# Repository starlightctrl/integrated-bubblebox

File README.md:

### TO-DO

Write read-me

#Integrated PCB for UMS Ultra's Bubblebox, based on Quark's Open Rectangle Template

 WIP

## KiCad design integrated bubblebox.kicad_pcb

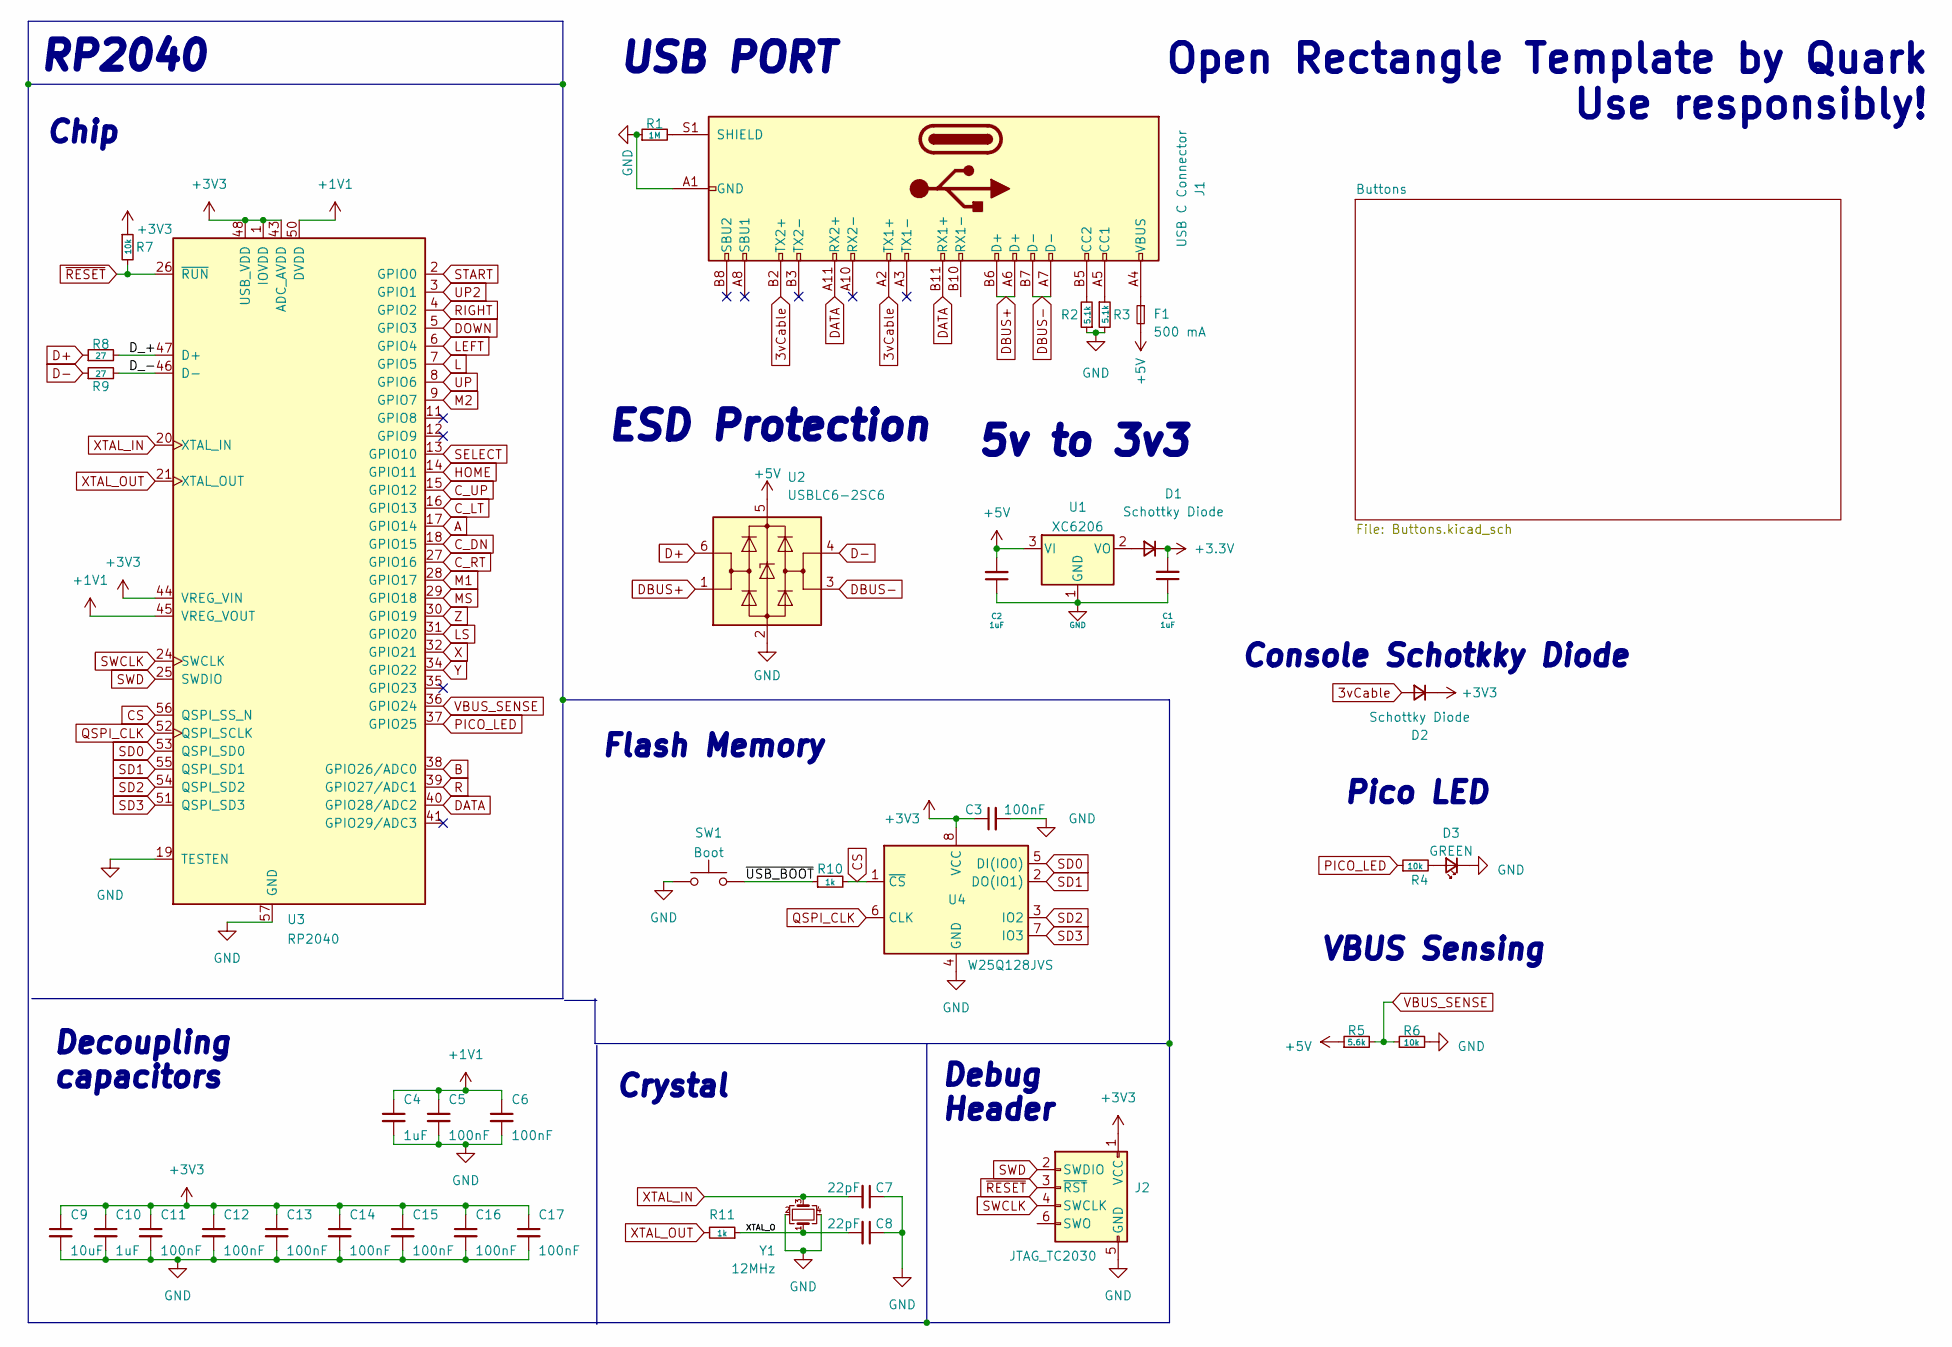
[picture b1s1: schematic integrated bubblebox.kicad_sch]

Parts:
C1, C2, C4, C10: 1uF; C_0402_1005Metric; LCSC C52923
C3, C5, C6, C11, C12, C13, C14, C15, C16, C17: 100nF; C_0402_1005Metric; LCSC C1525
C7, C8: 22pF; C_0402_1005Metric; LCSC C1555
C9: 10uF; C_0402_1005Metric; LCSC C15525
D1, D2: Schottky Diode; D_SOD-123; LCSC C8598
D3: GREEN; LED_0805_2012Metric; LCSC C2297
F1: 500 mA; Fuse_1206_3216Metric; LCSC C70076
J1: USB C Connector; TYPE-C_24P_QCHT; LCSC C456013
J2: JTAG_TC2030; Tag-Connect_TC2030-IDC-NL_2x03_P1.27mm_Vertical
R1: 1M; R_0603_1608Metric; LCSC C22935
R2, R3: 5.1k; R_0402_1005Metric; LCSC C25905
R4, R7: 10k; R_0402_1005Metric; LCSC C25744
R5: 5.6k; R_0603_1608Metric; LCSC C23189
R6: 10k; R_0603_1608Metric; LCSC C25804
R8, R9: 27; R_0603_1608Metric; LCSC C25190
R10, R11: 1k; R_0402_1005Metric; LCSC C11702
SW1: Boot; SW_SPST_SKQG_WithStem; LCSC C318884
U1: XC6206; SOT-23; LCSC C5446
U2: USBLC6-2SC6; SOT-23-6; LCSC C7519
U3: RP2040; RP2040-QFN-56; LCSC C2040
U4: W25Q128JVS; SOIC-8_5.23x5.23mm_P1.27mm; LCSC C97521
Y1: 12MHz; Crystal_SMD_3225-4Pin_3.2x2.5mm; LCSC C9002

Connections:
3vCable: D2.2 (A), J1.A2 (TX1+), J1.B2 (TX2+)
+1V1: C4.1, C5.1, C6.1, U3.23 (DVDD), U3.45 (VREG_VOUT), U3.50 (DVDD)
+5V: C2.2, F1.2, R5.1, U1.3 (VI), U2.5 (VBUS)
/D_+: R8.2, U3.47 (D+)
/D_-: R9.2, U3.46 (D-)
/XTAL_O: C8.2, R11.1, Y1.1
/~USB_BOOT: R10.1, SW1.2
A: U3.17 (GPIO14); also elsewhere on the board
B: U3.38 (GPIO26/ADC0); also elsewhere on the board
CS: R10.2, U3.56 (QSPI_SS_N), U4.1 (~CS)
C_DN: U3.18 (GPIO15); also elsewhere on the board
C_LT: U3.16 (GPIO13); also elsewhere on the board
C_RT: U3.27 (GPIO16); also elsewhere on the board
C_UP: U3.15 (GPIO12); also elsewhere on the board
D+: R8.1, U2.6 (I/O1)
D-: R9.1, U2.4 (I/O2)
DATA: J1.A11 (RX2+), J1.B11 (RX1+), U3.40 (GPIO28/ADC2)
DBUS+: J1.A6 (D+), J1.B6 (D+), U2.1 (I/O1)
DBUS-: J1.A7 (D-), J1.B7 (D-), U2.3 (I/O2)
GND: C1.1, C2.1, C3.2, C4.2, C5.2, C6.2, C7.1, C8.1, C9.2, C10.2, C11.2, C12.2, C13.2, C14.2, C15.2, C16.2, C17.2, D3.1 (K), J1.A1 (GND), J1.A12 (GND), J1.B1 (GND), J1.B12 (GND), J2.5 (GND), R1.1, R2.1, R3.2, R6.2, SW1.1, U1.1 (GND), U2.2 (GND), U3.19 (TESTEN), U3.57 (GND), U4.4 (GND), Y1.2, Y1.4; also elsewhere on the board
HOME: U3.14 (GPIO11); also elsewhere on the board
L: U3.7 (GPIO5); also elsewhere on the board
LEFT: U3.6 (GPIO4); also elsewhere on the board
LS: U3.31 (GPIO20); also elsewhere on the board
M1: U3.28 (GPIO17); also elsewhere on the board
M2: U3.9 (GPIO7); also elsewhere on the board
MS: U3.29 (GPIO18); also elsewhere on the board
unnamed: D1.2 (A), U1.2 (VO)
unnamed: D3.2 (A), R4.2
unnamed: F1.1, J1.A4 (VBUS), J1.A9 (VBUS), J1.B4 (VBUS), J1.B9 (VBUS)
unnamed: J1.A5 (CC1), R3.1
unnamed: J1.B5 (CC2), R2.2
unnamed: J1.S1 (SHIELD), R1.2
PICO_LED: R4.1, U3.37 (GPIO25)
QSPI_CLK: U3.52 (QSPI_SCLK), U4.6 (CLK)
R: U3.39 (GPIO27/ADC1); also elsewhere on the board
SD0: U3.53 (QSPI_SD0), U4.5 (DI(IO0))
SD1: U3.55 (QSPI_SD1), U4.2 (DO(IO1))
SD2: U3.54 (QSPI_SD2), U4.3 (IO2)
SD3: U3.51 (QSPI_SD3), U4.7 (IO3)
SELECT: U3.13 (GPIO10); also elsewhere on the board
START: U3.2 (GPIO0); also elsewhere on the board
SWCLK: J2.4 (SWCLK), U3.24 (SWCLK)
SWD: J2.2 (SWDIO), U3.25 (SWDIO)
UP: U3.8 (GPIO6); also elsewhere on the board
UP2: U3.3 (GPIO1); also elsewhere on the board
VBUS_SENSE: R5.2, R6.1, U3.36 (GPIO24)
X: U3.32 (GPIO21); also elsewhere on the board
XTAL_IN: C7.2, U3.20 (XTAL_IN), Y1.3
XTAL_OUT: R11.2, U3.21 (XTAL_OUT)
Y: U3.34 (GPIO22); also elsewhere on the board
Z: U3.30 (GPIO19); also elsewhere on the board
~RESET: J2.3 (~RST), R7.2, U3.26 (~RUN)

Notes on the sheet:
Console Schotkky Diode
Crystal
USB PORT
Flash Memory
Pico LED
Open Rectangle Template by Quark Use responsibly!
RP2040
Debug Header
VBUS Sensing
Chip
5v to 3v3
ESD Protection
Decoupling capacitors

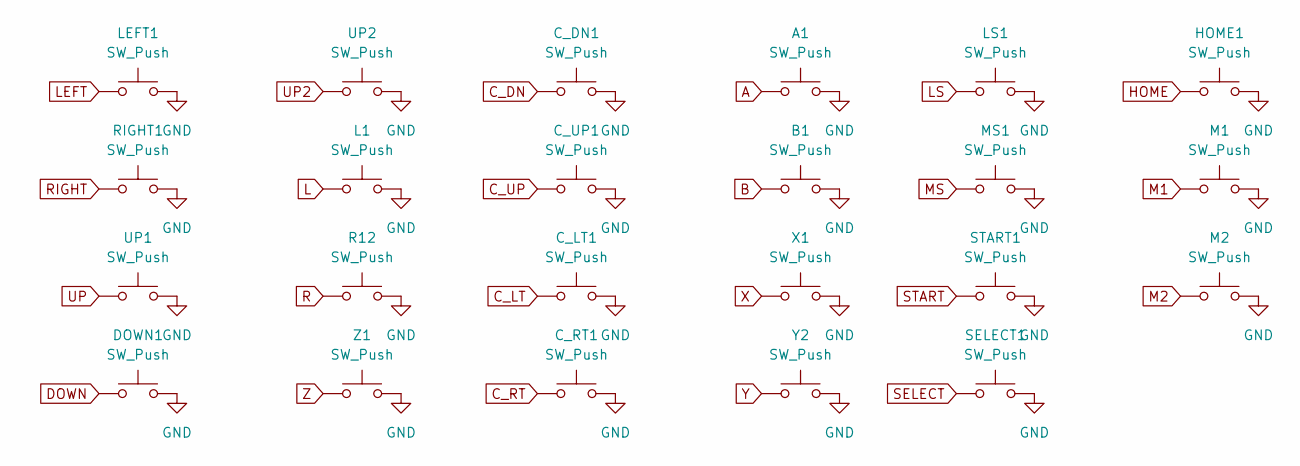
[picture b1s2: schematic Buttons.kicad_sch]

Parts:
A1: SW_Push; Kailh_socket_MX_optional
B1: SW_Push; Kailh_socket_MX_optional
C_DN1: SW_Push; Kailh_socket_MX_optional
C_LT1: SW_Push; Kailh_socket_MX_optional
C_RT1: SW_Push; Kailh_socket_MX_optional
C_UP1: SW_Push; Kailh_socket_MX_optional
DOWN1: SW_Push; Kailh_socket_MX_optional
HOME1: SW_Push; Kailh_socket_MX_optional
L1: SW_Push; Kailh_socket_MX_optional
LEFT1: SW_Push; Kailh_socket_MX_optional
LS1: SW_Push; Kailh_socket_MX_optional
M1, M2: SW_Push; Kailh_socket_MX_optional
MS1: SW_Push; Kailh_socket_MX_optional
R12: SW_Push; Kailh_socket_MX_optional
RIGHT1: SW_Push; Kailh_socket_MX_optional
SELECT1: SW_Push; Kailh_socket_MX_optional
START1: SW_Push; Kailh_socket_MX_optional
UP1, UP2: SW_Push; Kailh_socket_MX_optional
X1: SW_Push; Kailh_socket_MX_optional
Y2: SW_Push; Kailh_socket_MX_optional
Z1: SW_Push; Kailh_socket_MX_optional

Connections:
A: A1.1; also elsewhere on the board
B: B1.1; also elsewhere on the board
C_DN: C_DN1.1; also elsewhere on the board
C_LT: C_LT1.1; also elsewhere on the board
C_RT: C_RT1.1; also elsewhere on the board
C_UP: C_UP1.1; also elsewhere on the board
GND: A1.2, B1.2, C_DN1.2, C_LT1.2, C_RT1.2, C_UP1.2, DOWN1.2, HOME1.2, L1.2, LEFT1.2, LS1.2, M1.2, M2.2, MS1.2, R12.2, RIGHT1.2, SELECT1.2, START1.2, UP1.2, UP2.2, X1.2, Y2.2, Z1.2; also elsewhere on the board
HOME: HOME1.1; also elsewhere on the board
L: L1.1; also elsewhere on the board
LEFT: LEFT1.1; also elsewhere on the board
LS: LS1.1; also elsewhere on the board
M1: M1.1; also elsewhere on the board
M2: M2.1; also elsewhere on the board
MS: MS1.1; also elsewhere on the board
R: R12.1; also elsewhere on the board
SELECT: SELECT1.1; also elsewhere on the board
START: START1.1; also elsewhere on the board
UP: UP1.1; also elsewhere on the board
UP2: UP2.1; also elsewhere on the board
X: X1.1; also elsewhere on the board
Y: Y2.1; also elsewhere on the board
Z: Z1.1; also elsewhere on the board

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
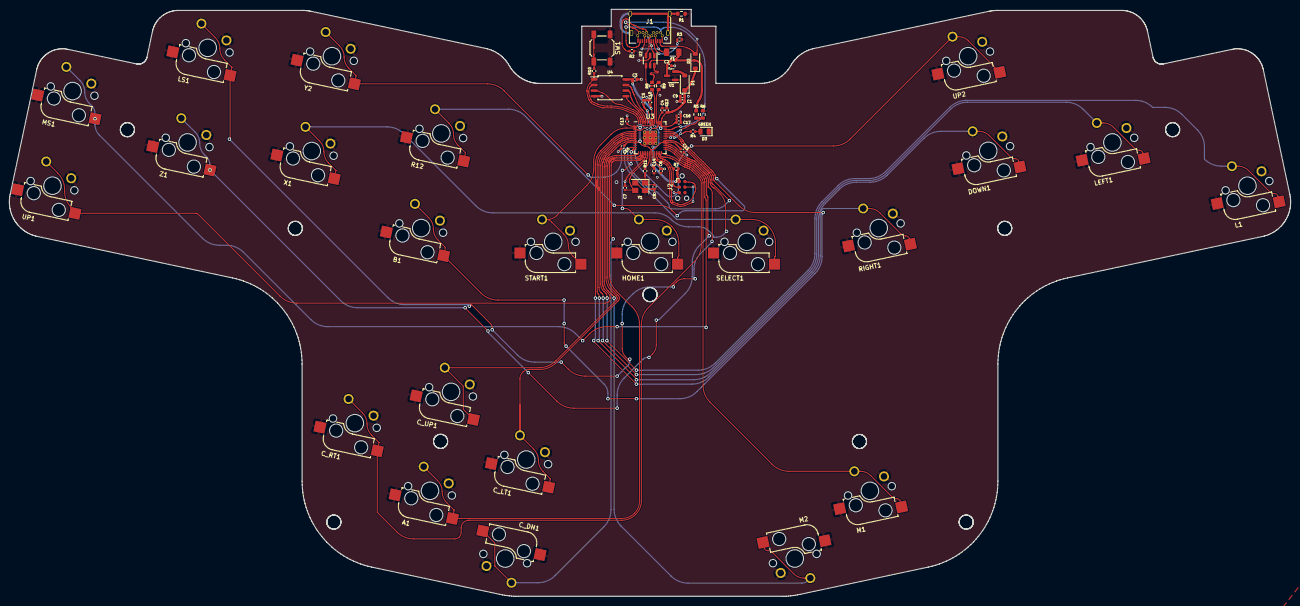
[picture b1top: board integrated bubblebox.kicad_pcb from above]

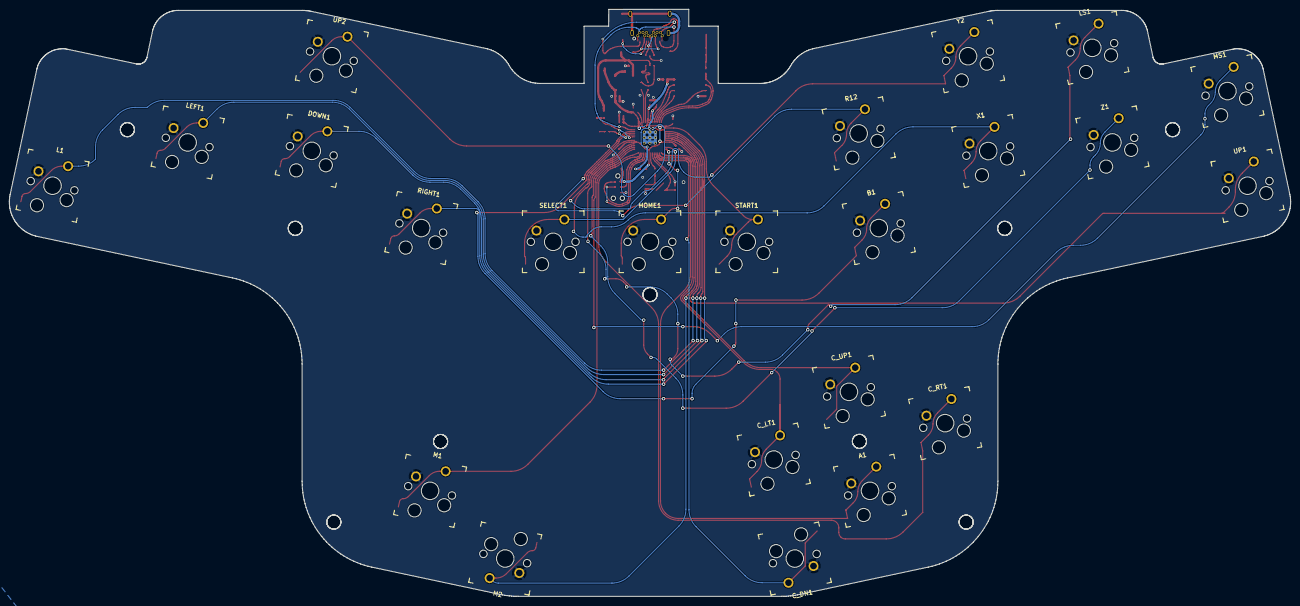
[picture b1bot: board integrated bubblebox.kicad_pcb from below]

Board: 2 copper layers, 291.3 x 133.4 mm, 63 parts (23 on the bottom side), 55 nets.

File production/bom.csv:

Designator,Footprint,Quantity,Value,LCSC Part #
"A1, B1, C_DN1, C_LT1, C_RT1, C_UP1, DOWN1, HOME1, L1, LEFT1, LS1, M1, M2, MS1, R12, RIGHT1, SELECT1, START1, UP1, UP2, X1, Y2, Z1",Kailh_socket_MX_optional,23,SW_Push,
"C1, C10, C2, C4",0402,4,1uF,C52923
"C11, C12, C13, C14, C15, C16, C17, C3, C5, C6",0402,10,100nF,C1525
"C7, C8",0402,2,22pF,C1555
C9,0402,1,10uF,C15525
"D1, D2",D_SOD-123,2,Schottky Diode,C8598
D3,0805,1,GREEN,C2297
F1,1206,1,500 mA,C70076
J1,TYPE-C_24P_QCHT,1,USB C Connector,C456013
R1,0603,1,1M,C22935
"R10, R11",0402,2,1k,C11702
"R2, R3",0402,2,5.1k,C25905
"R4, R7",0402,2,10k,C25744
R5,0603,1,5.6k,C23189
R6,0603,1,10k,C25804
"R8, R9",0603,2,27,C25190
SW1,SW_SPST_SKQG_WithStem,1,Boot,C318884
U1,SOT-23,1,XC6206,C5446
U2,SOT-23-6,1,USBLC6-2SC6,C7519
U3,RP2040-QFN-56,1,RP2040,C2040
U4,SOIC-8_5.23x5.23mm_P1.27mm,1,W25Q128JVS,C97521
Y1,Crystal_SMD_3225-4Pin_3.2x2.5mm,1,12MHz,C9002

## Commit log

2024-07-10 first commit integrated bubblebox
2024-07-10 Fixed hotswap connection on C-Up and C-Down, and also fixed RP2040 Gnd.
